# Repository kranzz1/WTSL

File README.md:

# WTSL
Online repository for documents and files related to SURE/WTSL
Updated and maintained by Zachary Kranz (kranzz1@udayton.edu) until 8/15/22. After that, you're on your own.

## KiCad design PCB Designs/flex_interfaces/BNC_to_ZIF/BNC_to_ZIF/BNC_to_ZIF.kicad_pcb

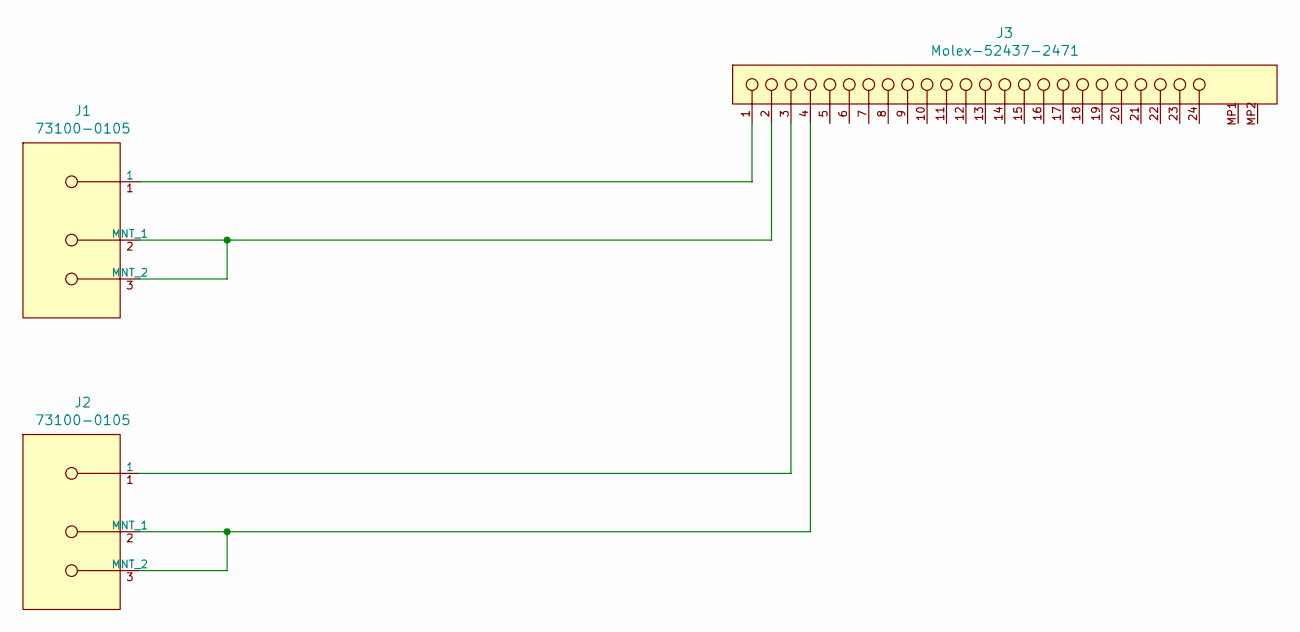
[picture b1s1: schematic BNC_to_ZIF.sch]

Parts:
J1, J2: 73100-0105; Molex-73100-0105-0-0-MFG; mouser part number 538-73100-0105; digikey description CONN BNC RCPT R/A 50 OHM PCB
J3: Molex-52437-2471; Molex-52437-2471-Manufacturer_Recommended; Voltage Max 50V

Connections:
unnamed: J1.1, J3.1
unnamed: J1.2 (MNT_1), J1.3 (MNT_2), J3.2
unnamed: J2.1, J3.3
unnamed: J2.2 (MNT_1), J2.3 (MNT_2), J3.4

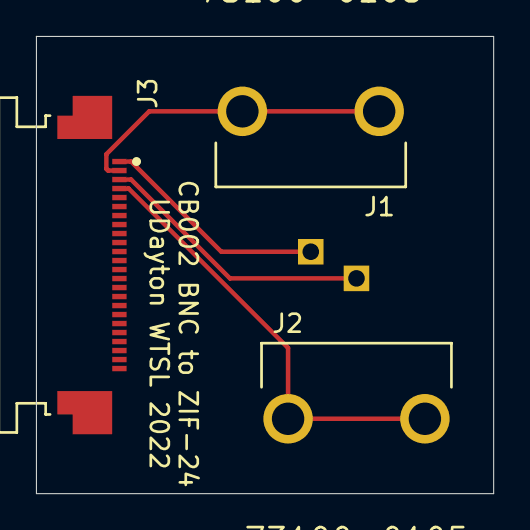
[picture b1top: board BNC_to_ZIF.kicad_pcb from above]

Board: 2 copper layers, 25.4 x 25.4 mm, 3 parts (0 on the bottom side), 4 nets.

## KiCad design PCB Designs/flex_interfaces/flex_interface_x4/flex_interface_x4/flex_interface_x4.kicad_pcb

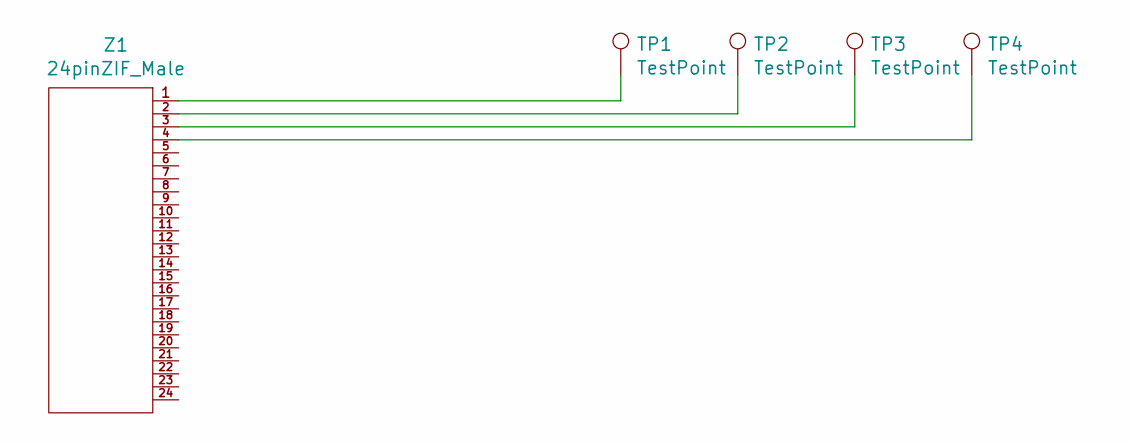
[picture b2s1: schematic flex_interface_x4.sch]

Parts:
TP1, TP2, TP3, TP4: TestPoint; TestPoint_Pad_D4.0mm
Z1: 24pinZIF_Male; 24Pin_ZIF_Flex

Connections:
unnamed: TP1.1, Z1.1
unnamed: TP2.1, Z1.2
unnamed: TP3.1, Z1.3
unnamed: TP4.1, Z1.4

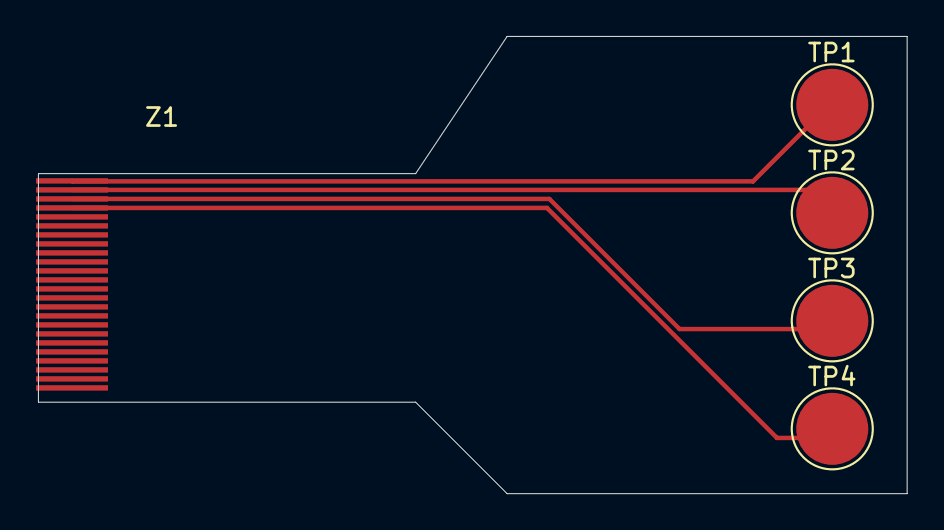
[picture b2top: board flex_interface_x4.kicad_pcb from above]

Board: 2 copper layers, 48.3 x 25.4 mm, 5 parts (0 on the bottom side), 4 nets.

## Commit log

2022-06-14 added pattern generator code
2022-06-15 added electrode tools
2022-06-15 added pcb designs
2022-06-16 added screenprinting spacer cad
2022-06-16 updated screen printing clip length
